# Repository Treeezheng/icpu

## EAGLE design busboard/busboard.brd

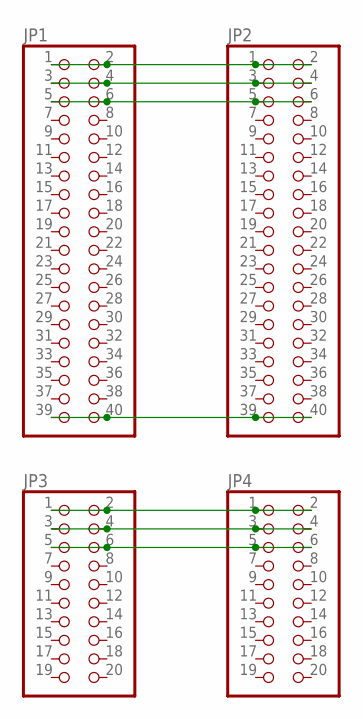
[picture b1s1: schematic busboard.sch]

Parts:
JP1, JP2: PINHD-2X20; 2X20
JP3, JP4: PINHD-2X10; 2X10

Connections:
unnamed: JP1.1, JP1.2, JP2.1, JP2.2
unnamed: JP1.3, JP1.4, JP2.3, JP2.4
unnamed: JP1.5, JP1.6, JP2.5, JP2.6
unnamed: JP1.39, JP1.40, JP2.39, JP2.40
unnamed: JP3.1, JP3.2, JP4.1, JP4.2
unnamed: JP3.3, JP3.4, JP4.3, JP4.4
unnamed: JP3.5, JP3.6, JP4.5, JP4.6

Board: 2 copper layers, 4 parts (0 on the bottom side), 7 nets, no tracks yet.

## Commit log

2021-08-05 add 74hc173 register experimental
2021-08-06 add busboard
2021-08-10 icpu cus123
2021-08-11 sync
2021-08-12 cpu input tristate buffer
2021-08-12 rm .dsstore
2021-08-13 05 addrams in cpu
2021-08-17 8 bit counter
2021-08-19 program counter
2021-08-20 icpu pc
2021-08-21 icpu ir
2021-08-22 icpu ir fix
2021-08-23 icpu control unit level 1 demo
2021-08-24 set a, ram preload
2021-08-24 fix debug desplay fix
2021-08-25 full controller complete
2021-08-26 instructions mirco codes and asm deasm
2021-08-27 add instructions
